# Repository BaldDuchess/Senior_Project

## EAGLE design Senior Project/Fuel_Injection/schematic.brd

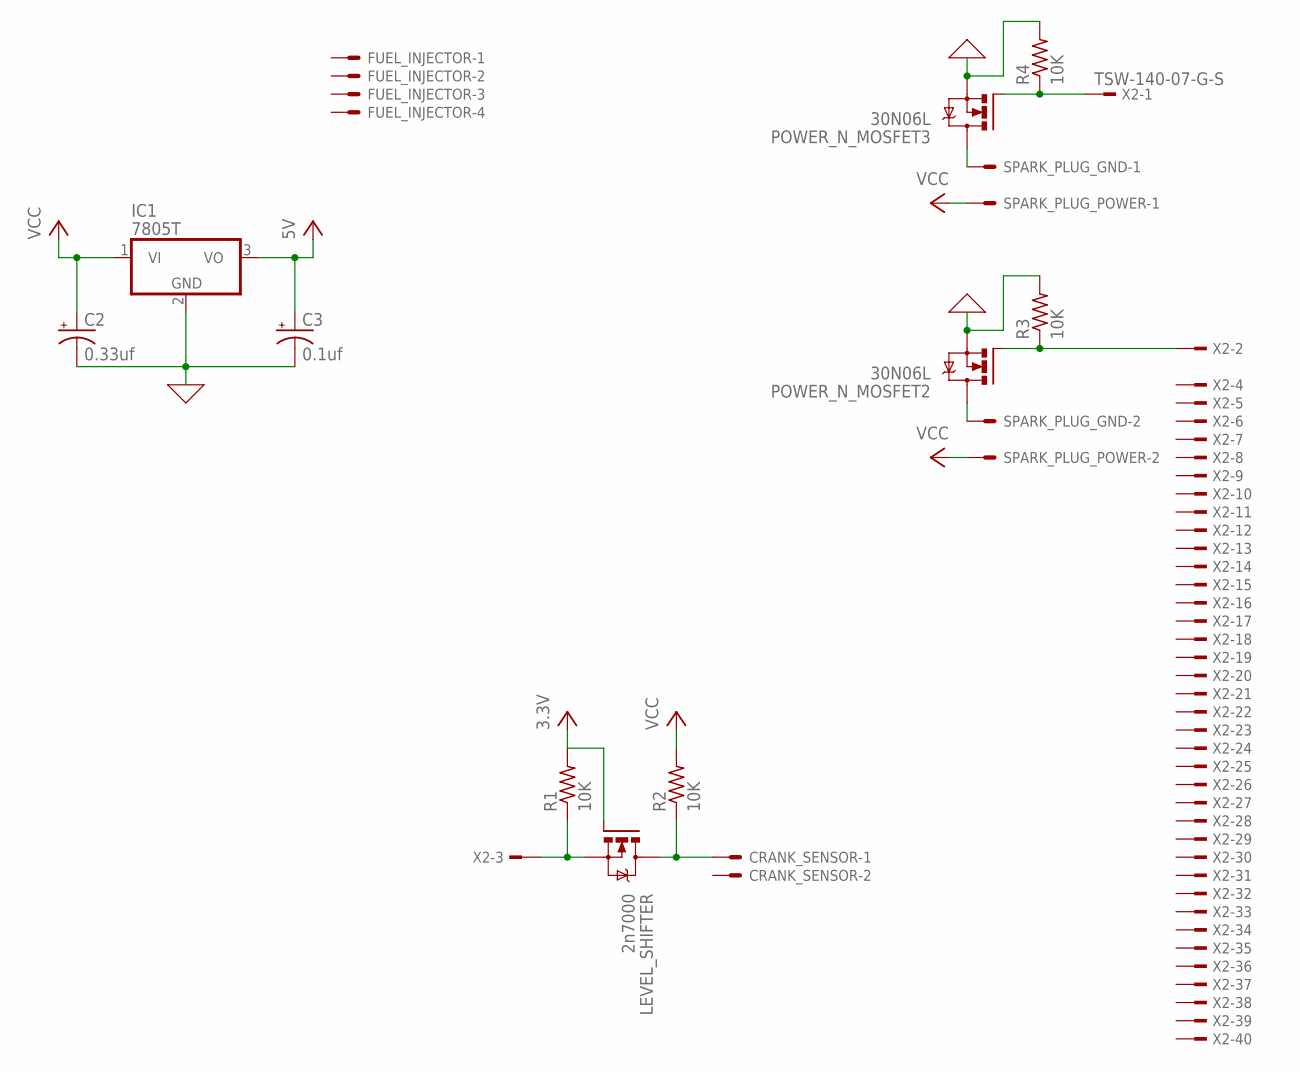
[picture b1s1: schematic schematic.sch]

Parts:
C2: 0.33uf; E2,5-5
C3: 0.1uf; E2,5-5
CRANK_SENSOR: KK-156-2
FUEL_INJECTOR: KK-156-4
IC1: 7805T; TO220H
LEVEL_SHIFTER: 2n7000; TO220BV
POWER_N_MOSFET2, POWER_N_MOSFET3: 30N06L; TO220BV
R1, R2, R3, R4: 10K; 0207/7
SPARK_PLUG_GND: KK-156-2
SPARK_PLUG_POWER: KK-156-2
X2: TSW-140-07-G-S; TSW-140-XX-G-S

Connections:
0: C2.-, C3.-, IC1.2 (GND), POWER_N_MOSFET2.S, POWER_N_MOSFET3.S, R3.2, R4.2
unnamed: POWER_N_MOSFET3.G, R4.1, X2.1
unnamed: POWER_N_MOSFET2.G, R3.1, X2.2
unnamed: POWER_N_MOSFET3.D, SPARK_PLUG_GND.1
unnamed: POWER_N_MOSFET2.D, SPARK_PLUG_GND.2
unnamed: LEVEL_SHIFTER.S, R1.1, X2.3
unnamed: LEVEL_SHIFTER.G, R1.2
unnamed: CRANK_SENSOR.1, LEVEL_SHIFTER.D, R2.1
VCC: C2.+, C3.+, IC1.1 (VI), IC1.3 (VO), R2.2, SPARK_PLUG_POWER.1, SPARK_PLUG_POWER.2

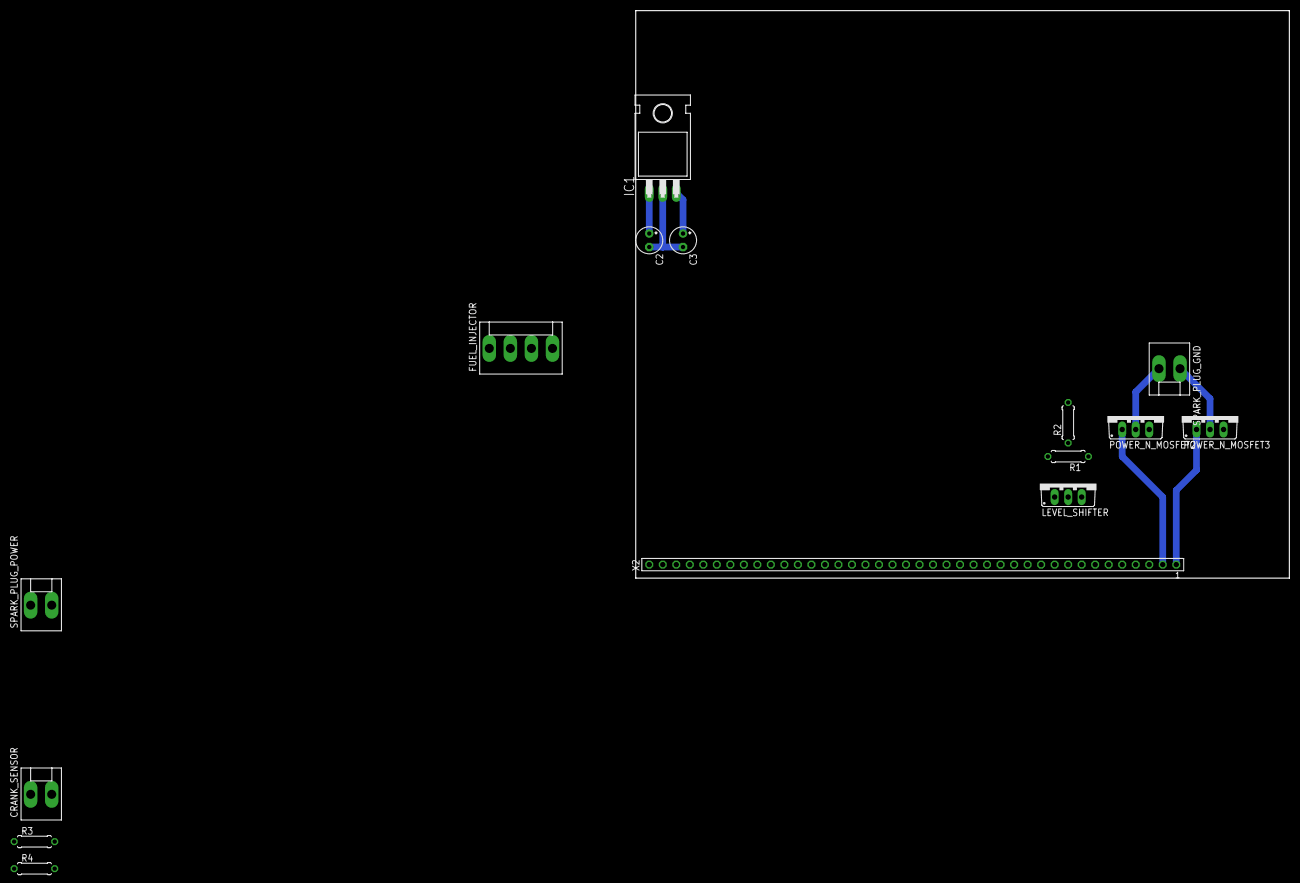
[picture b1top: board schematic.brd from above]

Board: 2 copper layers, 122.9 x 106.7 mm, 15 parts (0 on the bottom side), 9 nets.

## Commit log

2020-02-16 Added circuit schematic file
    Created file and added a few basic components.
2020-02-18 Added 129TM4C files
2020-03-26 Added initial crank signal sketch
